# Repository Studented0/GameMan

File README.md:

# GameMan

A handheld Game Boy emulator with a Fat form factor,  tactile buttons, 3.5" display, and USB-C for both charging and loading ROMs. Built around the ESP32-S3.

## Schematic

## PCB

Full schematic PDF: [GameMan.pdf](https://github.com/user-attachments/files/27543807/GameMan.pdf) 

## How it works

The ESP32-S3 runs Peanut-GB and drives a 3.5" SPI display. ROMs live on an SD card built into the display module. , drag a ROM onto it, unplug, and play. 

Battery charging goes through a TP4056. The ESP32 controls the charge enable pin in software so I can add things like charge limiting later. Battery voltage reads through a voltage divider on an ADC pin for a charge percentage estimate.

Controls are nine buttons total. The D-pad is a 5-button cluster with SELECT in the center. A, B, Start, and Menu sit on the right side.

## Specs

| Component | Part |
|---|---|
| MCU | ESP32-S3-DevKitC-1 N8R8 |
| Display | 3.5" IPS ST7796U, 480×320 |
| Touch | FT6336U over I2C |
| Storage | Micro SD (on display module) |
| Battery | 3.7V LiPo |
| Charging | TP4056 |
| Regulation | AMS1117-3.3 LDO |
| USB | USB-C, charging + OTG game loading |

Full BOM is in `/Production/bom.csv`.

## Repo structure

- `/KiCad` — schematic and PCB files
- `/Production` — gerbers, BOM, drill files
- `/Firmware` — in progress

## Status

PCB design done. Firmware not started yet

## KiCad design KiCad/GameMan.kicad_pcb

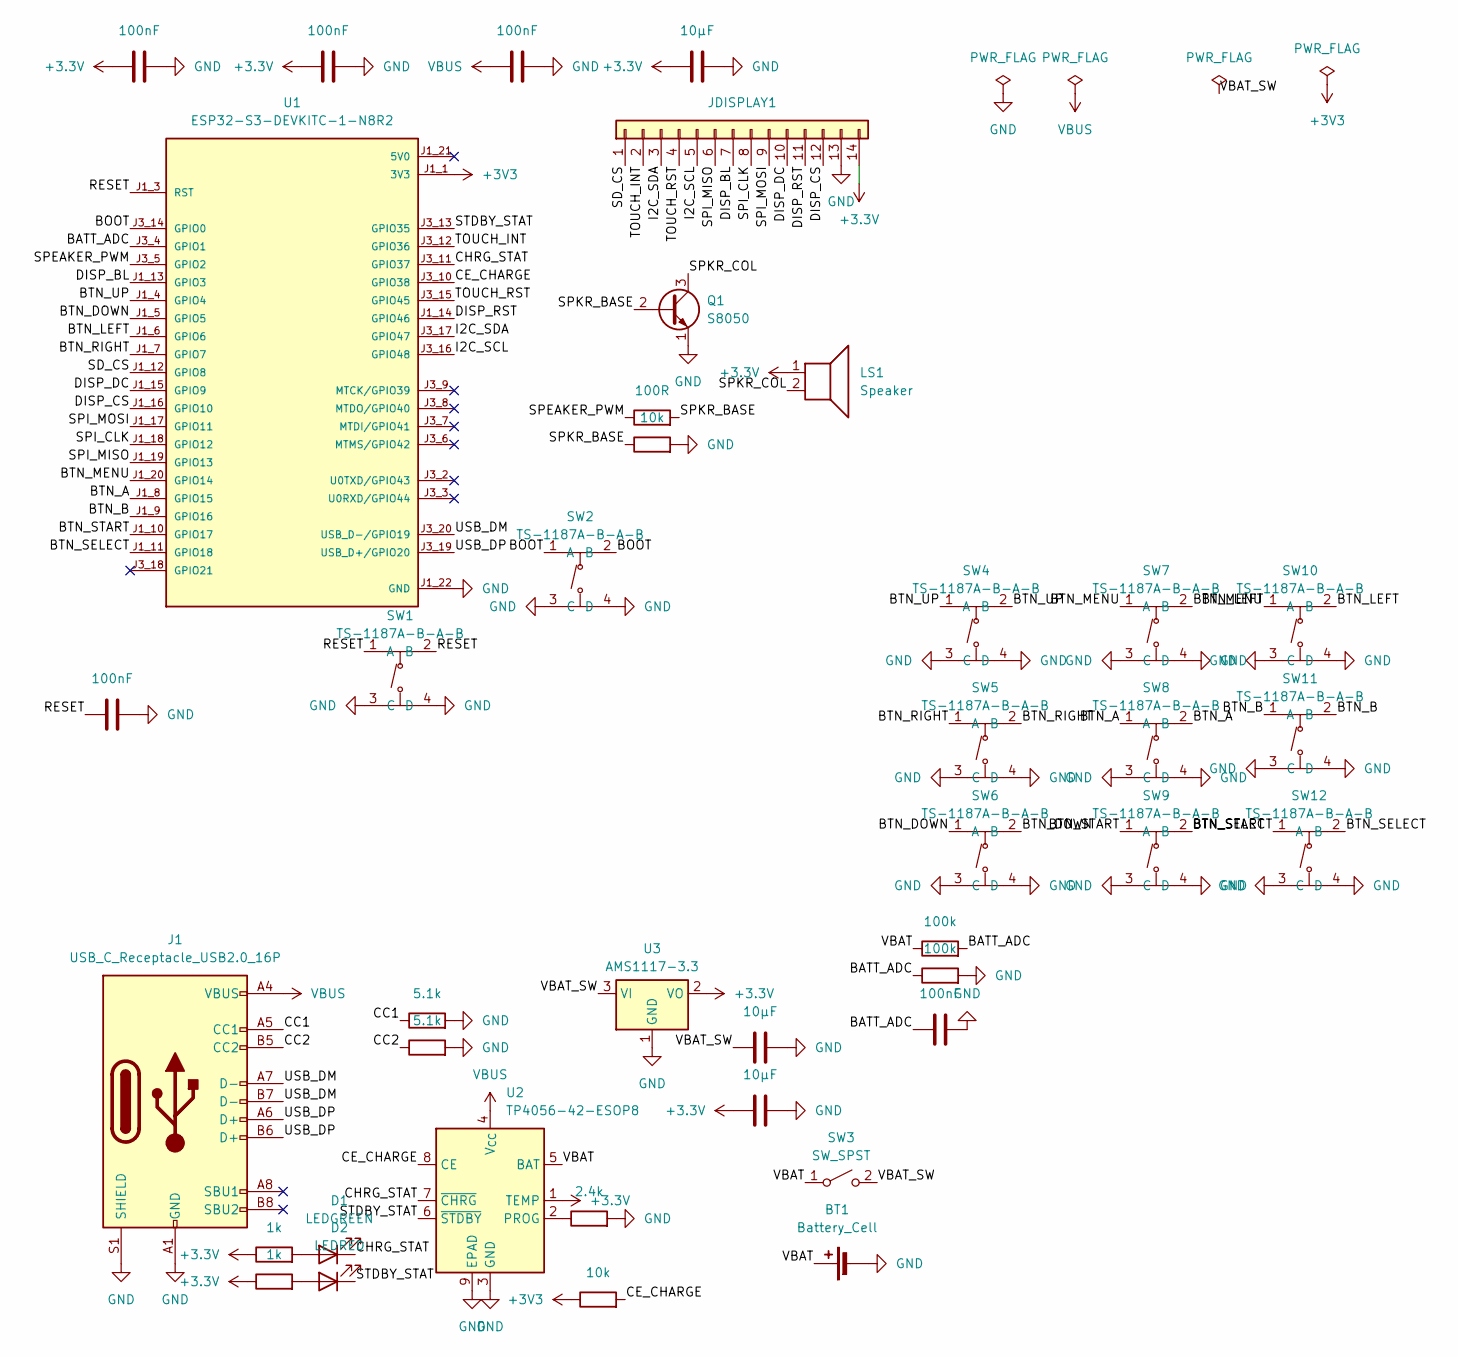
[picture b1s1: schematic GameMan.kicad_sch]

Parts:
BT1: Battery_Cell; JST_PH_B2B-PH-K_1x02_P2.00mm_Vertical
C1, C2, C3, C4, C8: 100nF; C_0402_1005Metric
C5, C6, C7: 10µF; C_0805_2012Metric
D1: LEDGREEN; LED_0402_1005Metric
D2: LEDRED; LED_0402_1005Metric
J1: USB_C_Receptacle_USB2.0_16P; USB_C_Receptacle_HRO_TYPE-C-31-M-12
JDISPLAY1: Conn_01x14; PinHeader_1x14_P2.54mm_Vertical
LS1: Speaker; PinHeader_1x02_P2.54mm_Vertical
Q1: S8050; SOT-23
R1, R2: 1k; R_0402_1005Metric
R3, R4: 5.1k; R_0402_1005Metric
R5: 2.4k; R_0402_1005Metric
R6, R8: 10k; R_0402_1005Metric
R7: 100R; R_0402_1005Metric
R9, R10: 100k; R_0402_1005Metric
SW1, SW2, SW4, SW5, SW6, SW7, SW8, SW9, SW10, SW11, SW12: TS-1187A-B-A-B; SW-SMD_4P-L5.1-W5.1-P3.70-LS6.5-TL_H1.5; MPN TS-1187A-B-A-B; LCSC Part C318884
SW3: SW_SPST; SW_SPDT_Shouhan_MSK12C02
U1: ESP32-S3-DEVKITC-1-N8R2; XCVR_ESP32-S3-DEVKITC-1-N8R2; PARTREV V1
U2: TP4056-42-ESOP8; SOIC-8-1EP_3.9x4.9mm_P1.27mm_EP2.41x3.3mm_ThermalVias
U3: AMS1117-3.3; SOT-223-3_TabPin2

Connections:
+3.3V: C2.1, C3.1, C5.1, C7.1, JDISPLAY1.14, LS1.1, R1.1, R2.1, U2.1 (TEMP), U3.2 (VO)
+3V3: R6.1, U1.J1_1 (3V3), U1.J1_2 (3V3)
/BATT_ADC: C8.1, R9.2, R10.1, U1.J3_4 (GPIO1)
/BOOT: SW2.1 (A), SW2.2 (B), U1.J3_14 (GPIO0)
/BTN_A: SW8.1 (A), SW8.2 (B), U1.J1_8 (GPIO15)
/BTN_B: SW11.1 (A), SW11.2 (B), U1.J1_9 (GPIO16)
/BTN_DOWN: SW6.1 (A), SW6.2 (B), U1.J1_5 (GPIO5)
/BTN_LEFT: SW10.1 (A), SW10.2 (B), U1.J1_6 (GPIO6)
/BTN_MENU: SW7.1 (A), SW7.2 (B), U1.J1_20 (GPIO14)
/BTN_RIGHT: SW5.1 (A), SW5.2 (B), U1.J1_7 (GPIO7)
/BTN_SELECT: SW12.1 (A), SW12.2 (B), U1.J1_11 (GPIO18)
/BTN_START: SW9.1 (A), SW9.2 (B), U1.J1_10 (GPIO17)
/BTN_UP: SW4.1 (A), SW4.2 (B), U1.J1_4 (GPIO4)
/CC1: J1.A5 (CC1), R3.1
/CC2: J1.B5 (CC2), R4.1
/CE_CHARGE: R6.2, U1.J3_10 (GPIO38), U2.8 (CE)
/CHRG_STAT: D1.1 (K), U1.J3_11 (GPIO37), U2.7 (~CHRG)
/DISP_BL: JDISPLAY1.7, U1.J1_13 (GPIO3)
/DISP_CS: JDISPLAY1.12, U1.J1_16 (GPIO10)
/DISP_DC: JDISPLAY1.10, U1.J1_15 (GPIO9)
/DISP_RST: JDISPLAY1.11, U1.J1_14 (GPIO46)
/I2C_SCL: JDISPLAY1.5, U1.J3_16 (GPIO48)
/I2C_SDA: JDISPLAY1.3, U1.J3_17 (GPIO47)
/RESET: C1.1, SW1.1 (A), SW1.2 (B), U1.J1_3 (RST)
/SD_CS: JDISPLAY1.1, U1.J1_12 (GPIO8)
/SPEAKER_PWM: R7.1, U1.J3_5 (GPIO2)
/SPI_CLK: JDISPLAY1.8, U1.J1_18 (GPIO12)
/SPI_MISO: JDISPLAY1.6, U1.J1_19 (GPIO13)
/SPI_MOSI: JDISPLAY1.9, U1.J1_17 (GPIO11)
/SPKR_BASE: Q1.2 (B), R7.2, R8.1
/SPKR_COL: LS1.2, Q1.3 (C)
/STDBY_STAT: D2.1 (K), U1.J3_13 (GPIO35), U2.6 (~STDBY)
/TOUCH_INT: JDISPLAY1.2, U1.J3_12 (GPIO36)
/TOUCH_RST: JDISPLAY1.4, U1.J3_15 (GPIO45)
/USB_DM: J1.A7 (D-), J1.B7 (D-), U1.J3_20 (USB_D-/GPIO19)
/USB_DP: J1.A6 (D+), J1.B6 (D+), U1.J3_19 (USB_D+/GPIO20)
/VBAT: BT1.1 (+), R9.1, SW3.1 (A), U2.5 (BAT)
/VBAT_SW: C6.1, SW3.2 (B), U3.3 (VI)
GND: BT1.2 (-), C1.2, C2.2, C3.2, C4.2, C5.2, C6.2, C7.2, C8.2, J1.A1 (GND), J1.A12 (GND), J1.B1 (GND), J1.B12 (GND), J1.S1 (SHIELD), JDISPLAY1.13, Q1.1 (E), R3.2, R4.2, R5.2, R8.2, R10.2, SW1.3 (C), SW1.4 (D), SW2.3 (C), SW2.4 (D), SW4.3 (C), SW4.4 (D), SW5.3 (C), SW5.4 (D), SW6.3 (C), SW6.4 (D), SW7.3 (C), SW7.4 (D), SW8.3 (C), SW8.4 (D), SW9.3 (C), SW9.4 (D), SW10.3 (C), SW10.4 (D), SW11.3 (C), SW11.4 (D), SW12.3 (C), SW12.4 (D), U1.J1_22 (GND), U1.J3_1 (GND), U1.J3_21 (GND), U1.J3_22 (GND), U2.3 (GND), U2.9 (EPAD), U3.1 (GND)
unnamed: D1.2 (A), R1.2
unnamed: D2.2 (A), R2.2
unnamed: R5.1, U2.2 (PROG)
VBUS: C4.1, J1.A4 (VBUS), J1.A9 (VBUS), J1.B4 (VBUS), J1.B9 (VBUS), U2.4 (V_{CC})

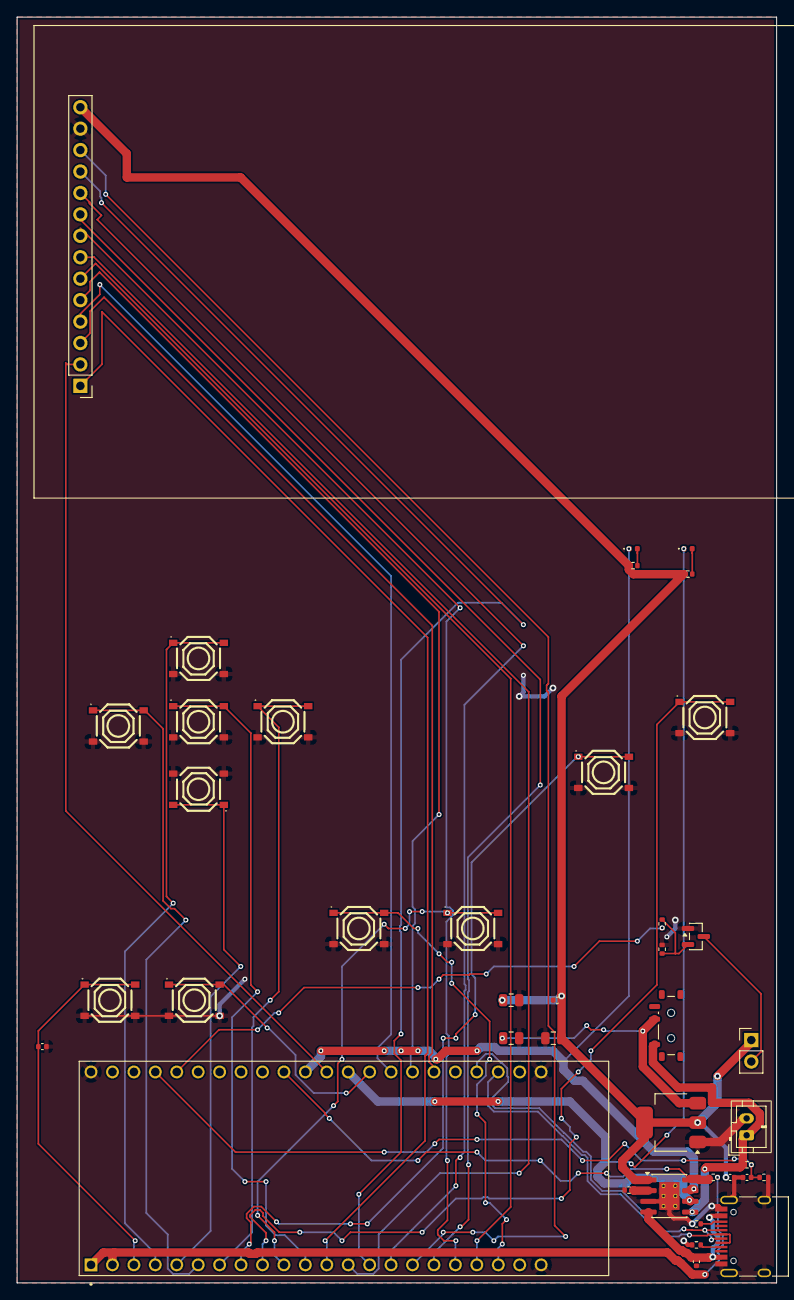
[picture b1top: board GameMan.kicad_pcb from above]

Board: 2 copper layers, 90.0 x 150.0 mm, 40 parts (0 on the bottom side), 43 nets.

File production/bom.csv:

Designator,Footprint,Quantity,Value,LCSC Part #
BT1,JST_PH_B2B-PH-K_1x02_P2.00mm_Vertical,1,Battery_Cell,
"C1, C2, C3, C4, C8",0402,5,100nF,
"C5, C6, C7",0805,3,10µF,
D1,0402,1,LEDGREEN,
D2,0402,1,LEDRED,
J1,USB_C_Receptacle_HRO_TYPE-C-31-M-12,1,USB_C_Receptacle_USB2.0_16P,
JDISPLAY1,PinHeader_1x14_P2.54mm_Vertical,1,Conn_01x14,
LS1,PinHeader_1x02_P2.54mm_Vertical,1,Speaker,
Q1,SOT-23,1,S8050,
"R1, R2",0402,2,1k,
"R10, R9",0402,2,100k,
"R3, R4",0402,2,5.1k,
R5,0402,1,2.4k,
"R6, R8",0402,2,10k,
R7,0402,1,100R,
"SW1, SW10, SW11, SW12, SW2, SW4, SW5, SW6, SW7, SW8, SW9",SW-SMD_4P-L5.1-W5.1-P3.70-LS6.5-TL_H1.5,11,TS-1187A-B-A-B,C318884
SW3,SW_SPDT_Shouhan_MSK12C02,1,SW_SPST,
U1,XCVR_ESP32-S3-DEVKITC-1-N8R2,1,ESP32-S3-DEVKITC-1-N8R2,
U2,SOIC-8-1EP_3.9x4.9mm_P1.27mm_EP2.41x3.3mm_ThermalVias,1,TP4056-42-ESOP8,
U3,SOT-223-3_TabPin2,1,AMS1117-3.3,

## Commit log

2026-05-09 PCB layout complete
2026-05-09 Enhance README with screenshots and PDF link
    Added screenshots and a PDF link to the README.
2026-05-09 images and README
2026-05-10 Polish README and reorganize folders
2026-05-10 Update README with additional schematic image
    Added an image to the schematic section and updated the text.
2026-05-14 Add project file
